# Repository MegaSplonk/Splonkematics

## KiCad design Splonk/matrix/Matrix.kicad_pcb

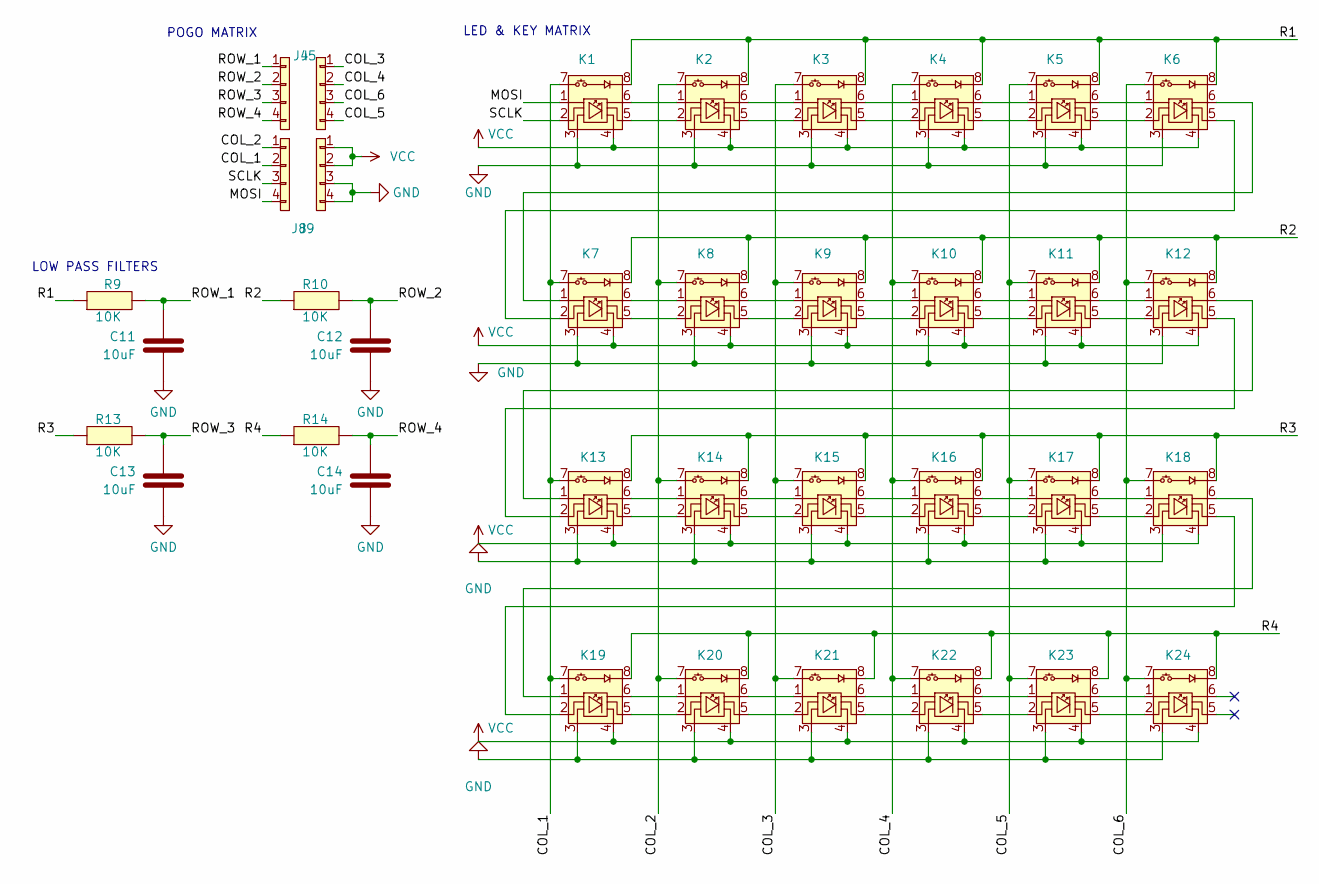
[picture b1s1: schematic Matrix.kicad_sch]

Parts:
C11, C12, C13, C14: 10uF; Capacitor_0603
J4, J5, J8, J9: POGO; Pogo_4_pin_female
K1, K2, K3, K4, K5, K6, K7, K8, K9, K10, K11, K12, K13, K14, K15, K16, K17, K18, K19, K20, K21, K22, K23, K24: APA102; Kailh_socket_MX_APA102_combo
R9, R10, R13, R14: 10K; Resistor_0603

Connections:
/COL_1: J8.2, K1.7, K7.7, K13.7, K19.7
/COL_2: J8.1, K2.7, K8.7, K14.7, K20.7
/COL_3: J5.1, K3.7, K9.7, K15.7, K21.7
/COL_4: J5.2, K4.7, K10.7, K16.7, K22.7
/COL_5: J5.4, K5.7, K11.7, K17.7, K23.7
/COL_6: J5.3, K6.7, K12.7, K18.7, K24.7
/MOSI: J8.4, K1.1 (D^{in})
/R1: K1.8, K2.8, K3.8, K4.8, K5.8, K6.8, R9.1
/R2: K7.8, K8.8, K9.8, K10.8, K11.8, K12.8, R10.1
/R3: K13.8, K14.8, K15.8, K16.8, K17.8, K18.8, R13.1
/R4: K19.8, K20.8, K21.8, K22.8, K23.8, K24.8, R14.1
/ROW_1: C11.1, J4.1, R9.2
/ROW_2: C12.1, J4.2, R10.2
/ROW_3: C13.1, J4.3, R13.2
/ROW_4: C14.1, J4.4, R14.2
/SCLK: J8.3, K1.2 (C^{in})
GND: C11.2, C12.2, C13.2, C14.2, J9.3, J9.4, K1.3 (GND), K2.3 (GND), K3.3 (GND), K4.3 (GND), K5.3 (GND), K6.3 (GND), K7.3 (GND), K8.3 (GND), K9.3 (GND), K10.3 (GND), K11.3 (GND), K12.3 (GND), K13.3 (GND), K14.3 (GND), K15.3 (GND), K16.3 (GND), K17.3 (GND), K18.3 (GND), K19.3 (GND), K20.3 (GND), K21.3 (GND), K22.3 (GND), K23.3 (GND), K24.3 (GND)
unnamed: K1.5 (C^{out}), K2.2 (C^{in})
unnamed: K1.6 (D^{out}), K2.1 (D^{in})
unnamed: K2.5 (C^{out}), K3.2 (C^{in})
unnamed: K2.6 (D^{out}), K3.1 (D^{in})
unnamed: K3.5 (C^{out}), K4.2 (C^{in})
unnamed: K3.6 (D^{out}), K4.1 (D^{in})
unnamed: K4.5 (C^{out}), K5.2 (C^{in})
unnamed: K4.6 (D^{out}), K5.1 (D^{in})
unnamed: K5.5 (C^{out}), K6.2 (C^{in})
unnamed: K5.6 (D^{out}), K6.1 (D^{in})
unnamed: K6.5 (C^{out}), K7.2 (C^{in})
unnamed: K6.6 (D^{out}), K7.1 (D^{in})
unnamed: K7.5 (C^{out}), K8.2 (C^{in})
unnamed: K7.6 (D^{out}), K8.1 (D^{in})
unnamed: K8.5 (C^{out}), K9.2 (C^{in})
unnamed: K8.6 (D^{out}), K9.1 (D^{in})
unnamed: K9.5 (C^{out}), K10.2 (C^{in})
unnamed: K10.5 (C^{out}), K11.2 (C^{in})
unnamed: K9.6 (D^{out}), K10.1 (D^{in})
unnamed: K10.6 (D^{out}), K11.1 (D^{in})
unnamed: K11.5 (C^{out}), K12.2 (C^{in})
unnamed: K11.6 (D^{out}), K12.1 (D^{in})
unnamed: K12.5 (C^{out}), K13.2 (C^{in})
unnamed: K12.6 (D^{out}), K13.1 (D^{in})
unnamed: K13.5 (C^{out}), K14.2 (C^{in})
unnamed: K13.6 (D^{out}), K14.1 (D^{in})
unnamed: K14.5 (C^{out}), K15.2 (C^{in})
unnamed: K14.6 (D^{out}), K15.1 (D^{in})
unnamed: K15.5 (C^{out}), K16.2 (C^{in})
unnamed: K15.6 (D^{out}), K16.1 (D^{in})
unnamed: K16.5 (C^{out}), K17.2 (C^{in})
unnamed: K16.6 (D^{out}), K17.1 (D^{in})
unnamed: K17.5 (C^{out}), K18.2 (C^{in})
unnamed: K17.6 (D^{out}), K18.1 (D^{in})
unnamed: K18.5 (C^{out}), K19.2 (C^{in})
unnamed: K18.6 (D^{out}), K19.1 (D^{in})
unnamed: K19.5 (C^{out}), K20.2 (C^{in})
unnamed: K19.6 (D^{out}), K20.1 (D^{in})
unnamed: K20.5 (C^{out}), K21.2 (C^{in})
unnamed: K20.6 (D^{out}), K21.1 (D^{in})
unnamed: K21.5 (C^{out}), K22.2 (C^{in})
unnamed: K21.6 (D^{out}), K22.1 (D^{in})
unnamed: K22.5 (C^{out}), K23.2 (C^{in})
unnamed: K22.6 (D^{out}), K23.1 (D^{in})
unnamed: K23.5 (C^{out}), K24.2 (C^{in})
unnamed: K23.6 (D^{out}), K24.1 (D^{in})
VCC: J9.1, J9.2, K1.4 (VCC), K2.4 (VCC), K3.4 (VCC), K4.4 (VCC), K5.4 (VCC), K6.4 (VCC), K7.4 (VCC), K8.4 (VCC), K9.4 (VCC), K10.4 (VCC), K11.4 (VCC), K12.4 (VCC), K13.4 (VCC), K14.4 (VCC), K15.4 (VCC), K16.4 (VCC), K17.4 (VCC), K18.4 (VCC), K19.4 (VCC), K20.4 (VCC), K21.4 (VCC), K22.4 (VCC), K23.4 (VCC), K24.4 (VCC)

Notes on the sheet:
LED & KEY MATRIX
POGO MATRIX
LOW PASS FILTERS

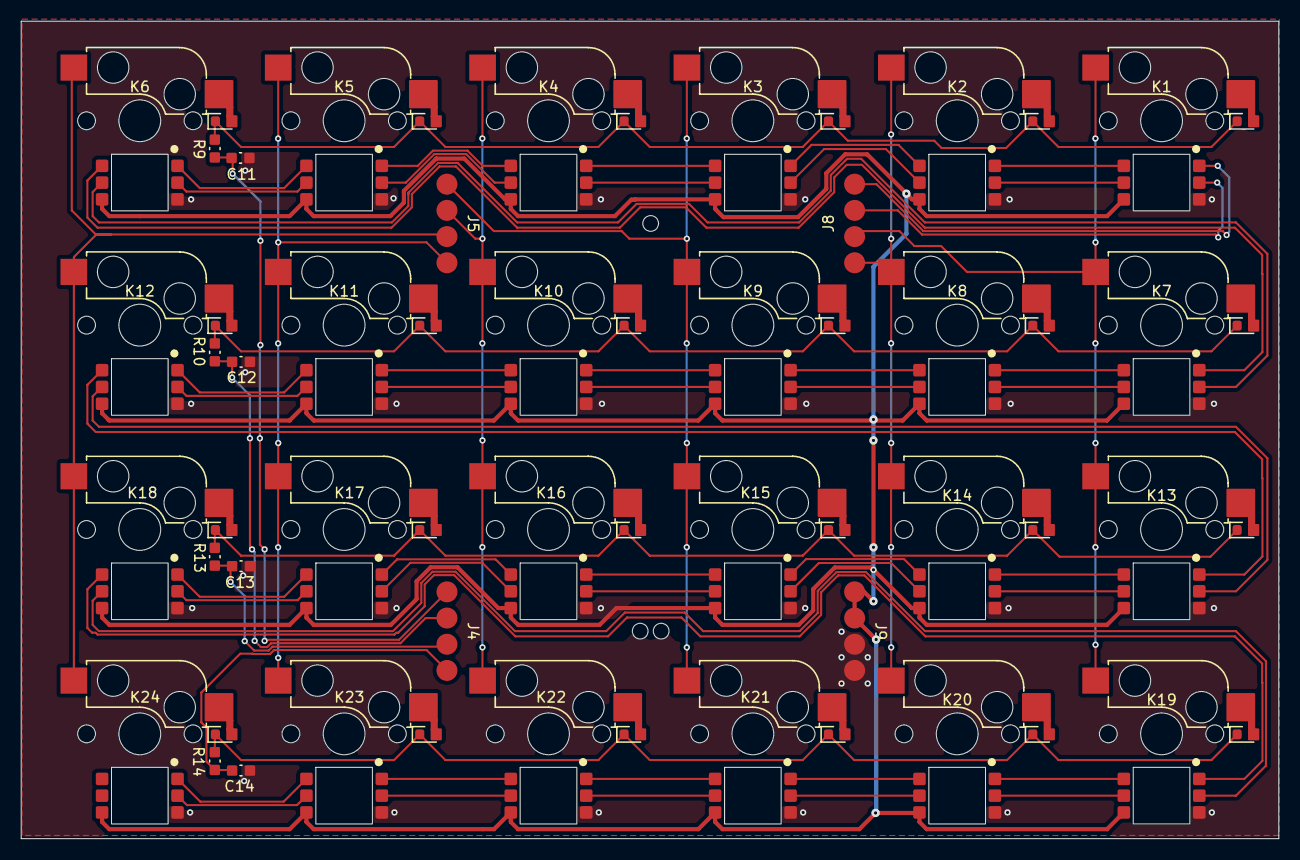
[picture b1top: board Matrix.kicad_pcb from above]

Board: 2 copper layers, 120.0 x 78.0 mm, 39 parts (0 on the bottom side), 64 nets.

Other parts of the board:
AH1, AH2, AH3: Alignment_Hole

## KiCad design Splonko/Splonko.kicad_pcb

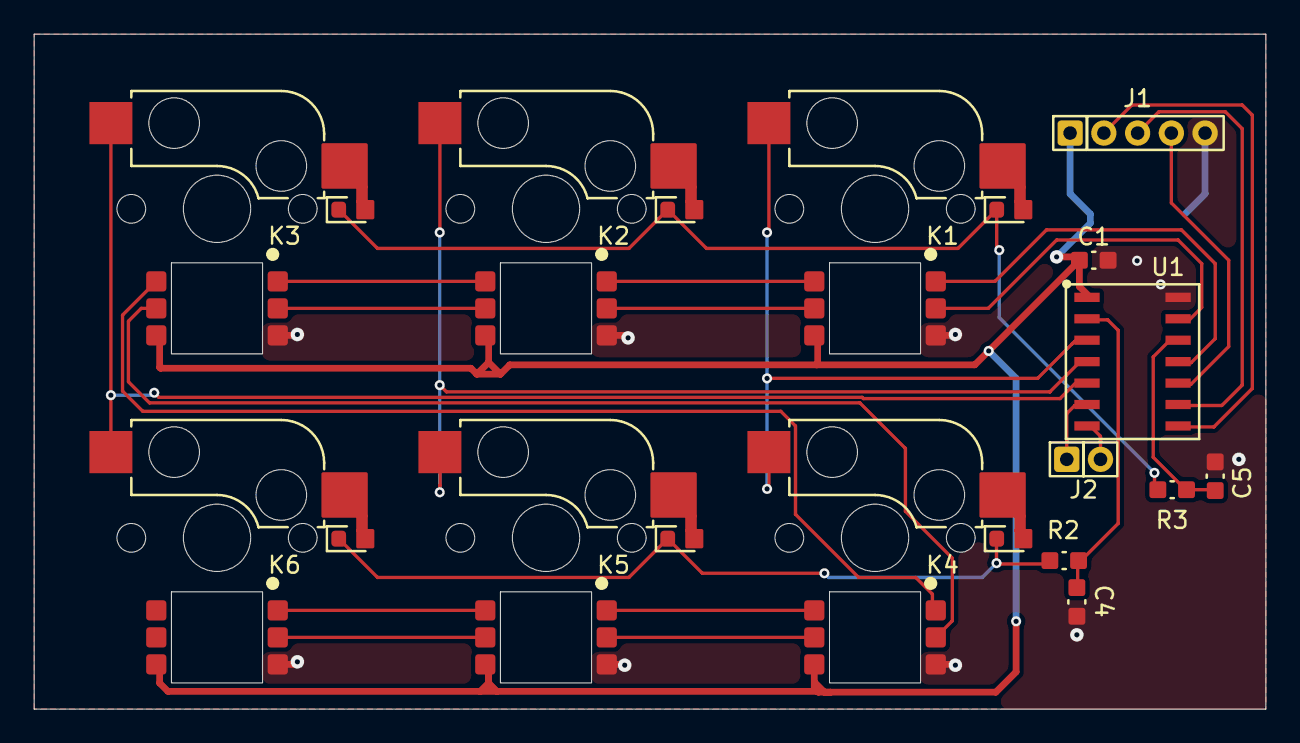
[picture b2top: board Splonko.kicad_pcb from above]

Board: 2 copper layers, 73.0 x 40.0 mm, 15 parts (1 on the bottom side), 26 nets.

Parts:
C1: 10nF; Capacitor_0603
C2: 100uF; ElectroliticCapacitor
C4, C5: 10uF; Capacitor_0603
J1: SplonkConn; MaixCon-5P
J2: UART; MaixCon-2P
K1, K2, K3, K4, K5, K6: Kailh_socket_MX_APA102_combo
R2, R3: 10K; Resistor_0603
U1: Attiny1614; SOIC-14

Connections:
/COL1: K1.7, K4.7, U1.3 (PA5)
/COL2: K2.7, K5.7, U1.4 (PA6)
/COL3: K3.7, K6.7, U1.5 (PA7)
/MOSI: K1.1 (D^{in}), U1.11 (PA1)
/R1: K1.8, K2.8, K3.8, R3.1
/R2: K4.8, K5.8, K6.8, R2.1
/ROW1: C5.1, R3.2, U1.12 (PA2)
/ROW2: C4.1, R2.2, U1.2 (PA4)
/RX: J2.1, U1.6 (TX/PB3)
/SCL: J1.3, U1.9 (SCL/PB0)
/SCLK: K1.2 (C^{in}), U1.13 (PA3)
/SDA: J1.2, U1.8 (SDA/PB1)
/TX: J2.2, U1.7 (RX/PB2)
/UPDI: J1.4, U1.10 (UPDI/PA0)
GND: C1.2, C2.-, C4.2, C5.2, J1.5, K1.3 (GND), K2.3 (GND), K3.3 (GND), K4.3 (GND), K5.3 (GND), K6.3 (GND), U1.14 (GND)
unnamed: K1.5 (C^{out}), K2.2 (C^{in})
unnamed: K1.6 (D^{out}), K2.1 (D^{in})
unnamed: K2.5 (C^{out}), K3.2 (C^{in})
unnamed: K2.6 (D^{out}), K3.1 (D^{in})
unnamed: K3.5 (C^{out}), K4.2 (C^{in})
unnamed: K3.6 (D^{out}), K4.1 (D^{in})
unnamed: K4.5 (C^{out}), K5.2 (C^{in})
unnamed: K4.6 (D^{out}), K5.1 (D^{in})
unnamed: K5.5 (C^{out}), K6.2 (C^{in})
unnamed: K5.6 (D^{out}), K6.1 (D^{in})
VCC: C1.1, C2.+, J1.1, K1.4 (VCC), K2.4 (VCC), K3.4 (VCC), K4.4 (VCC), K5.4 (VCC), K6.4 (VCC), U1.1 (VCC)

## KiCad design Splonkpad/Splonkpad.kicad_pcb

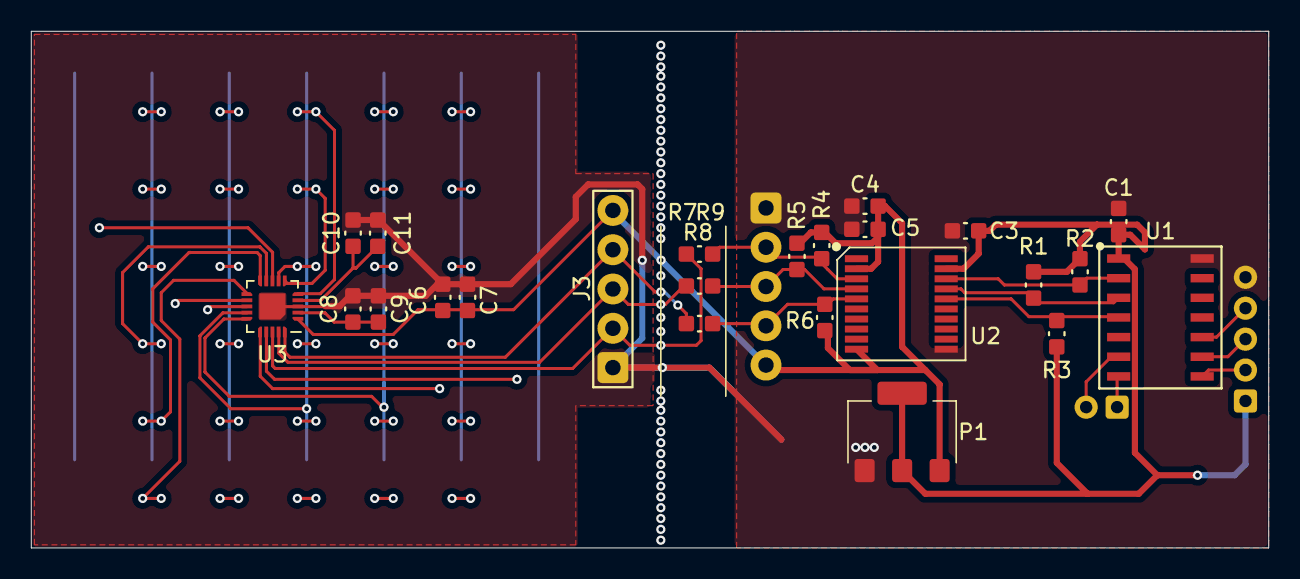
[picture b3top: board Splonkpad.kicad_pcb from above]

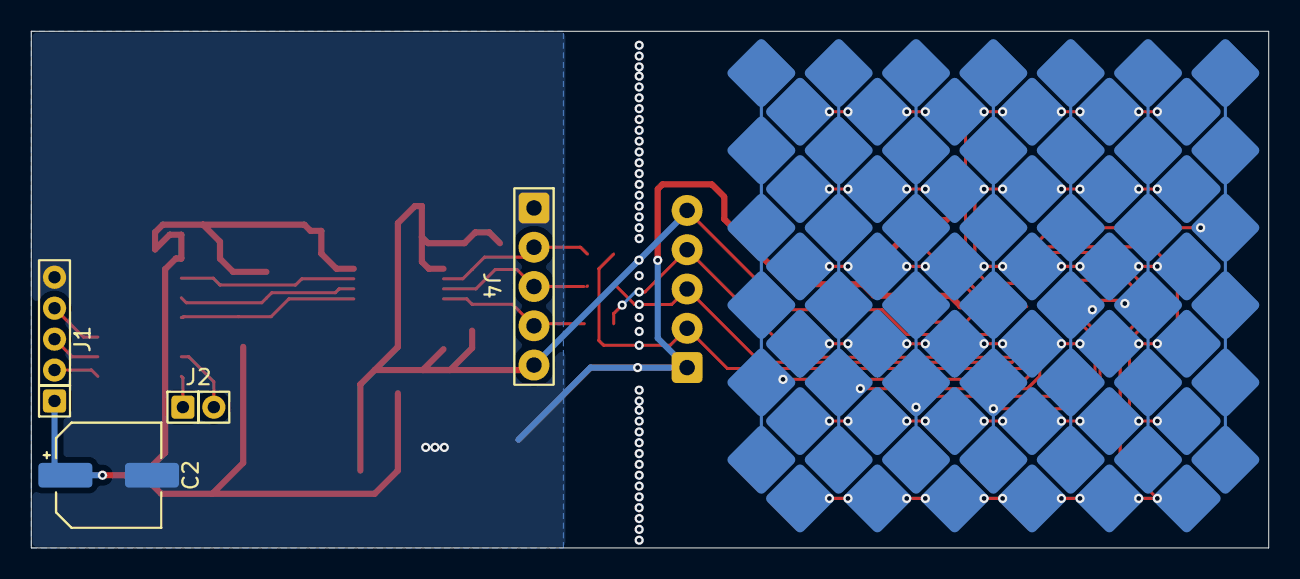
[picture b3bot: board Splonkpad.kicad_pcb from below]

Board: 2 copper layers, 80.0 x 33.4 mm, 106 parts (82 on the bottom side), 32 nets.

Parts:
C1: 10nF; Capacitor_0603
C2: 100uF; ElectroliticCapacitor
C3, C4: 100nF; Capacitor_0603
C5: 10uF; Capacitor_0603
C6, C8, C10: 100pF; Capacitor_0603
C7: 4.7uF; Capacitor_0603
C9, C11: 2.2uF; Capacitor_0603
J1: SplonkConn; MaixCon-5P
J2: UART; MaixCon-2P
J3, J4: Pad Conn; Pin_header_5
P1: AMS1117-3.3; AMS1117
P2, P3, P4, P5, P6, P7, P8, P9, P10, P11, P12, P13, P14, P15, P16, P17, P18, P19, P20, P21, P22, P23, P24, P25, P26, P27, P28, P29, P30, P31, P32, P33, P34, P35, P36, P37, P38, P39, P40, P41, P42, P43, P44, P45, P46, P47, P48, P49, P50, P51, P52, P53, P54, P55, P56, P57, P58, P59, P60, P61, P62, P63, P64, P65, P66, P67, P68, P69, P70, P71, P72, P73, P74, P75, P76, P77, P78, P79: Pad
R1, R2, R4, R5: 4.7K; Resistor_0603
R3, R6: 10K; Resistor_0603
R7, R8, R9: 0; Resistor_0603
U1: ATtiny1614-SS; SOIC-14
U2: TXS0108EPW; TSSOP-20
U3: IQS7211E; QFN-20_EP_3x3_Pitch0.4mm-

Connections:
3.3V: C4.1, C5.1, C6.1, C7.1, J3.5, J4.5, P1.3 (V^{in}), R4.1, R5.1, R6.2, U2.2 (VCCA), U2.10 (OE), U3.1 (VDD)
/RX: J2.1, U1.7 (RX/PB2)
/RX0: P8.1, P20.1, P32.1, P44.1, P56.1, P68.1, U3.5 (RX0/TX0)
/RX1: P9.1, P21.1, P33.1, P45.1, P57.1, P69.1, U3.6 (RX1/TX1)
/RX2: P10.1, P22.1, P34.1, P46.1, P58.1, P70.1, U3.7 (RX2/TX2)
/RX4: P11.1, P23.1, P35.1, P47.1, P59.1, P71.1, U3.9 (RX4/TX4)
/RX5: P12.1, P24.1, P36.1, P48.1, P60.1, P72.1, U3.10 (RX5/TX5)
/RX6: P13.1, P25.1, P37.1, P49.1, P61.1, P73.1, U3.11 (RX6/TX6)
/SCL: J1.3, U1.9 (SCL/PB0)
/SCL^{3.3P}: J3.2, R7.2, U3.18 (SCL)
/SCL^{3.3S}: J4.2, R4.2, R7.1, U2.3 (A2)
/SDA: J1.2, U1.8 (SDA/PB1)
/SDA^{3.3P}: J3.3, R8.2, U3.19 (SDA)
/SDA^{3.3S}: J4.3, R5.2, R8.1, U2.4 (A3)
/TX: J2.2, U1.6 (TX/PB3)
/TX3: P2.1, P3.1, P4.1, P5.1, P6.1, P7.1, U3.8 (RX3/TX3)
/TX7: P14.1, P15.1, P16.1, P17.1, P18.1, P19.1, U3.12 (RX7/TX7)
/TX8: P26.1, P27.1, P28.1, P29.1, P30.1, P31.1, U3.13 (TX8)
/TX9: P38.1, P39.1, P40.1, P41.1, P42.1, P43.1, U3.14 (TX9)
/TX10: P50.1, P51.1, P52.1, P53.1, P54.1, P55.1, U3.15 (TX10)
/TX11: P62.1, P63.1, P64.1, P65.1, P66.1, P67.1, U3.16 (TX11)
/TX12: P74.1, P75.1, P76.1, P77.1, P78.1, P79.1, U3.17 (TX12)
/UPDI: J1.4, U1.10 (UPDI/PA0)
/VREGA: C10.1, C11.1, U3.4 (VREGA)
/VREGD: C8.1, C9.1, U3.2 (VREGD)
/~RST^{3.3P}: J3.4, R9.2, U3.20 (RDY)
/~RST^{3.3S}: J4.4, R6.1, R9.1, U2.5 (A4)
GND: C1.2, C2.-, C3.2, C4.2, C5.2, C6.2, C7.2, C8.2, C9.2, C10.2, C11.2, J1.5, J3.1, J4.1, P1.1 (GND), U1.14 (GND), U2.11 (GND), U3.3 (VSS), U3.21 (GND_TAB)
unnamed: R2.2, U1.2 (PA4), U2.18 (B2)
unnamed: R1.2, U1.3 (PA5), U2.17 (B3)
unnamed: R3.1, U1.4 (PA6), U2.16 (B4)
VCC: C1.1, C2.+, C3.1, J1.1, P1.2 (V^{out}), P1.4 (V^{out}), R1.1, R2.1, R3.2, U1.1 (VCC), U2.19 (VCCB)
